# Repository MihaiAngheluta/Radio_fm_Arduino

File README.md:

Receiver Radio FM With Arduino

For this project i used the following components:

- Arduino Nano;
- Radio receiver module RDA5807;
- Antenna spiral from copper;
- Display LCD 16x2;
- Adjustable resistor of 10 kohmi;
- Potentiometer B10K;
- Leds of different colors;
- Resistor of 390 ohmi;
- Breadboard;
- Female Audio Jack of 3.5 mm;
- Wires for conections between components.

For the radio module RDA5807 was realised breakout.

Conections between radio module and arduino nano:

- SDA  pinul A4;
- SCL  pinul A5;
- VDD  3.3V;
- GND  GND.

Conections between display lcd and arduino nano:

- Pinul 1 la Ground;
- Pinul 2 la 5V;
- Pinul 3 la semireglabil;
- Pinul 4 - RS (Data/Instruction Select) la pinul digital 12;
- Pinul 5 la Ground;
- Pinul 6 - Enable la pinul digital 11;
- Pinul 11- D4 la pinul digital 5;
- Pinul 12 - D5 la pinul digital 4;
- Pinul 13 - D6 la pinul digital 3;
- Pinul 14 - D7 la pinul digital 2;
- Pinul 15 la rezistenta de 390 ohmi si pinul 16 la Ground.

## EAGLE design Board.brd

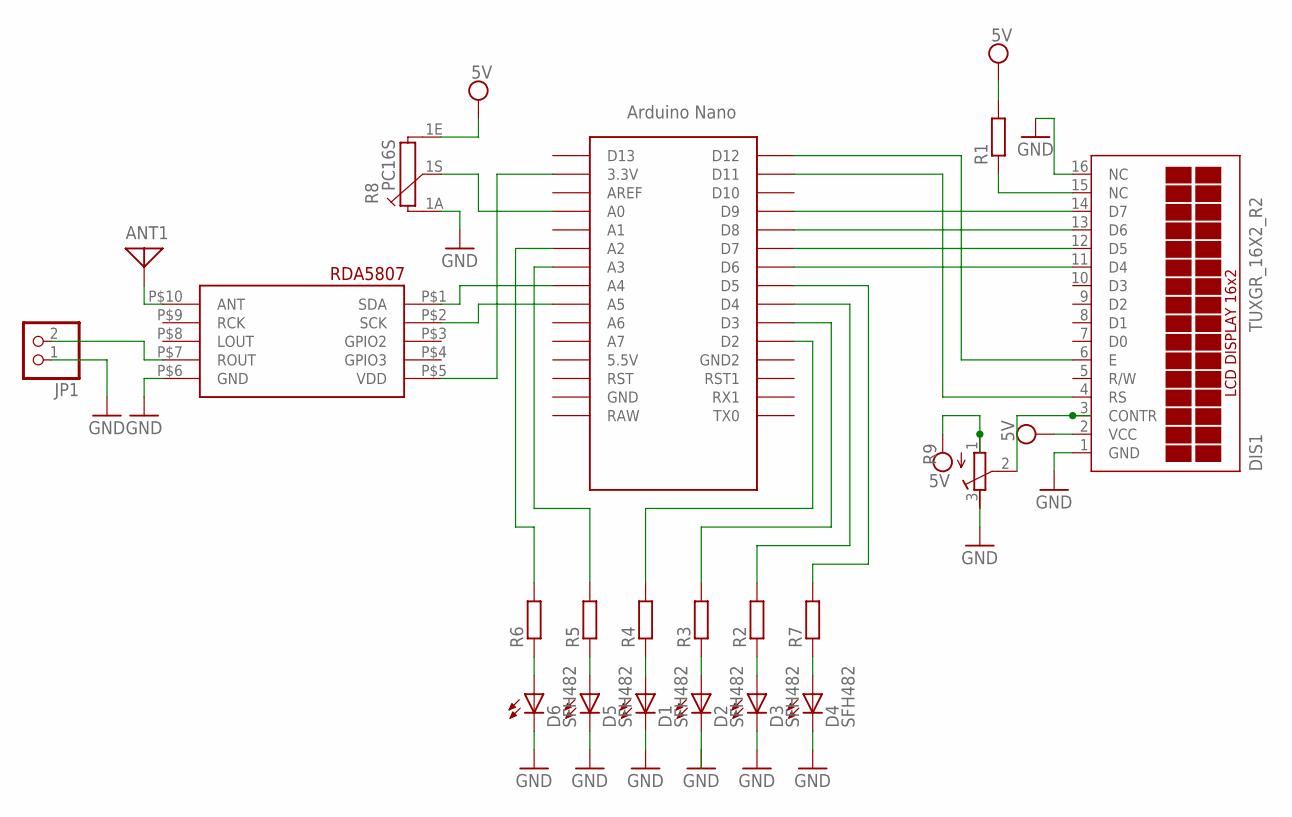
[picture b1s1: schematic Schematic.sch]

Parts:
ANT1: ANTENNA; PAD-01
D1, D2, D3, D4, D5, D6: SFH482
DIS1: TUXGR_16X2_R2
JP1: PINHD-1X2; 1X02
R1, R2, R3, R4, R5, R6, R7: R-EU_0207/10; 0207/10
R8: PC16S
R9: R-TRIMM3339P; RTRIM3339P
U$1: NANO
U$3: RDA5807

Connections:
GND: D1.K (C), D2.K (C), D3.K (C), D4.K (C), D5.K (C), D6.K (C), DIS1.1 (GND), DIS1.16 (NC), JP1.1, R8.1A, R9.3 (A), U$3.P$6 (GND)
unnamed: D6.A, R6.1
unnamed: D5.A, R5.1
unnamed: D1.A, R4.1
unnamed: D2.A, R3.1
unnamed: D3.A, R2.1
unnamed: D4.A, R7.1
unnamed: DIS1.11 (D4), U$1.D6
unnamed: U$1.A5, U$3.P$2 (SCK)
unnamed: JP1.2, U$3.P$7 (ROUT)
unnamed: DIS1.12 (D5), U$1.D7
unnamed: R8.1S, U$1.A0
unnamed: DIS1.13 (D6), U$1.D8
unnamed: DIS1.14 (D7), U$1.D9
unnamed: DIS1.3 (CONTR), R9.2 (S)
unnamed: DIS1.6 (E), U$1.D12
unnamed: DIS1.4 (RS), U$1.D11
unnamed: R4.2, U$1.D2
unnamed: R3.2, U$1.D3
unnamed: R2.2, U$1.D4
unnamed: R7.2, U$1.D5
unnamed: R5.2, U$1.A3
unnamed: R6.2, U$1.A2
unnamed: DIS1.15 (NC), R1.1
unnamed: U$1.3.3V, U$3.P$5 (VDD)
unnamed: ANT1.1, U$3.P$10 (ANT)
unnamed: U$1.A4, U$3.P$1 (SDA)
VSS: DIS1.2 (VCC), R1.2, R8.1E, R9.1 (E)

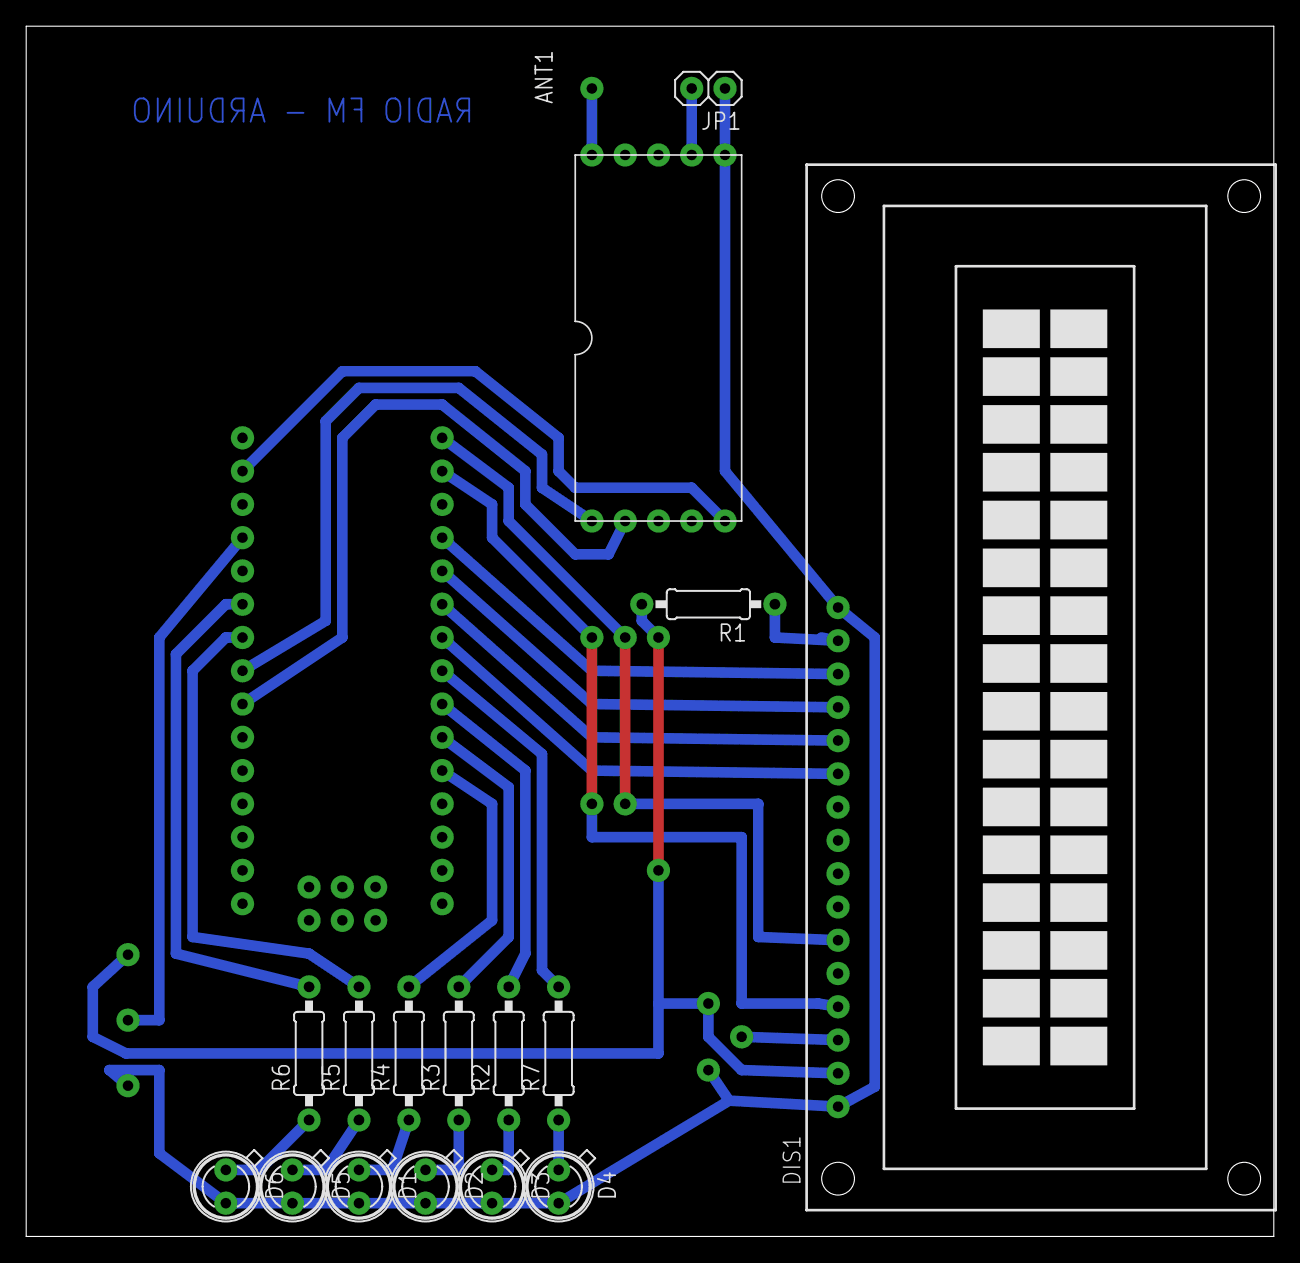
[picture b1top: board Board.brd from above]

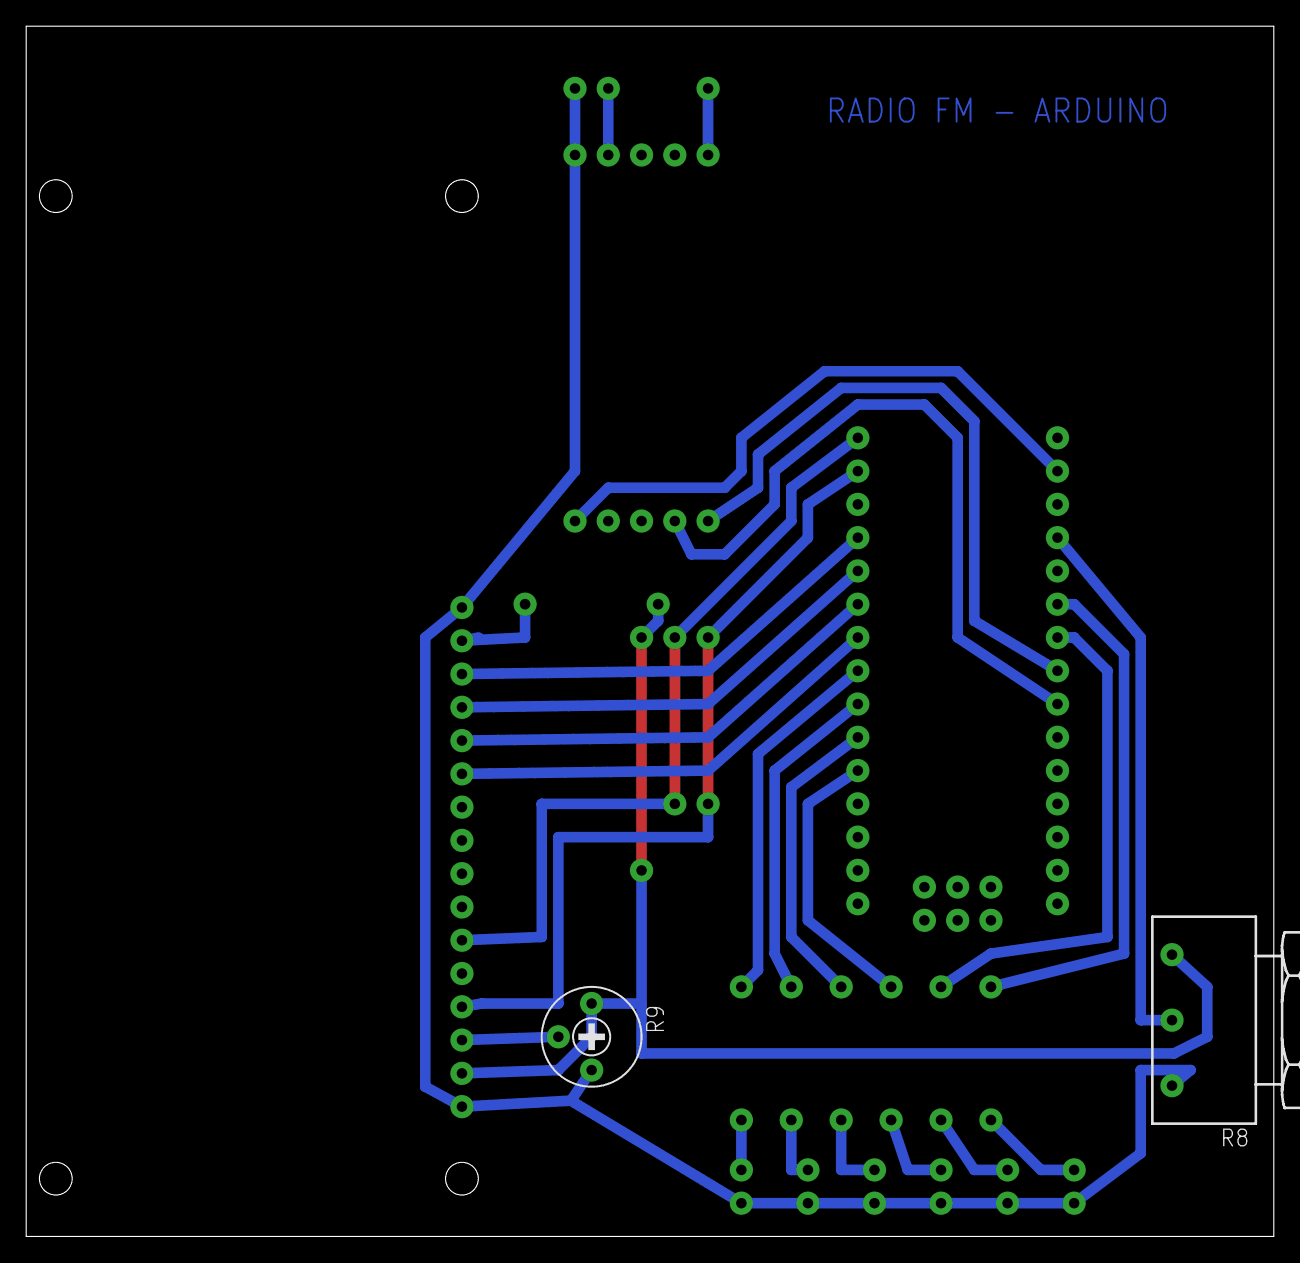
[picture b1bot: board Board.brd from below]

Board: 2 copper layers, 95.2 x 92.4 mm, 20 parts (2 on the bottom side), 28 nets.

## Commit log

2019-02-26 Libraries for Display and Radio Module
2019-02-26 Board with updated library pads position and dimensions
2019-02-26 Board pdf for print
2019-02-26 Add the readme file
2019-02-26 Add readme file
